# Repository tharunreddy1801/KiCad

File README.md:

# 🛠️ PCB Design Using KiCad

## 📘 Overview

This project demonstrates the complete process of designing a **Printed Circuit Board (PCB)** for a **blinking LED circuit** using a **555 timer IC**. It covers schematic creation, PCB layout, component placement, routing, and final manufacturing file preparation. This guide is ideal for hobbyists and engineers aiming to develop compact and reliable custom PCBs.

---

## 🔍 Project Objective

- Design a PCB to control blinking LEDs using a 555 timer IC  
- Utilize **KiCad**, a free and open-source EDA software  
- Achieve a compact, efficient, and manufacturable PCB design  

---

## ⚙️ System Components

### 📐 Schematic Design
- Complete circuit schematic detailing all component values and connections  
- Ensures correct pin assignments and circuit functionality  

### 🗺️ PCB Layout
- Board outline defined to fit project requirements  
- Components placed for logical routing and ease of manufacturing  
- Focus on:  
  - Signal integrity  
  - Power distribution  
  - Thermal management  

---

## 📸 Design Visualization

---

## ✅ Design Verification

- Design Rule Checks (DRC) performed to identify spacing and connection errors  
- Electrical Rules Checks (ERC) ensure correctness of schematic-to-board mappings  
- Validation to confirm manufacturability and reliability  

---

## 💾 Files Included

- **Schematics:** Detailed circuit diagrams for assembly and troubleshooting  
- **PCB Layout Files:** Component placement and trace routing data  
- **Gerber Files:** Industry-standard output for PCB fabrication  

---

## 🚀 Getting Started

- Open the project files using **KiCad** software suite  
- Follow included documentation for setup and build instructions  
- Review schematic and layout for customization or enhancements  

---

## 👨‍💻 Author

**Yennam Sai Tharun Reddy** ✨

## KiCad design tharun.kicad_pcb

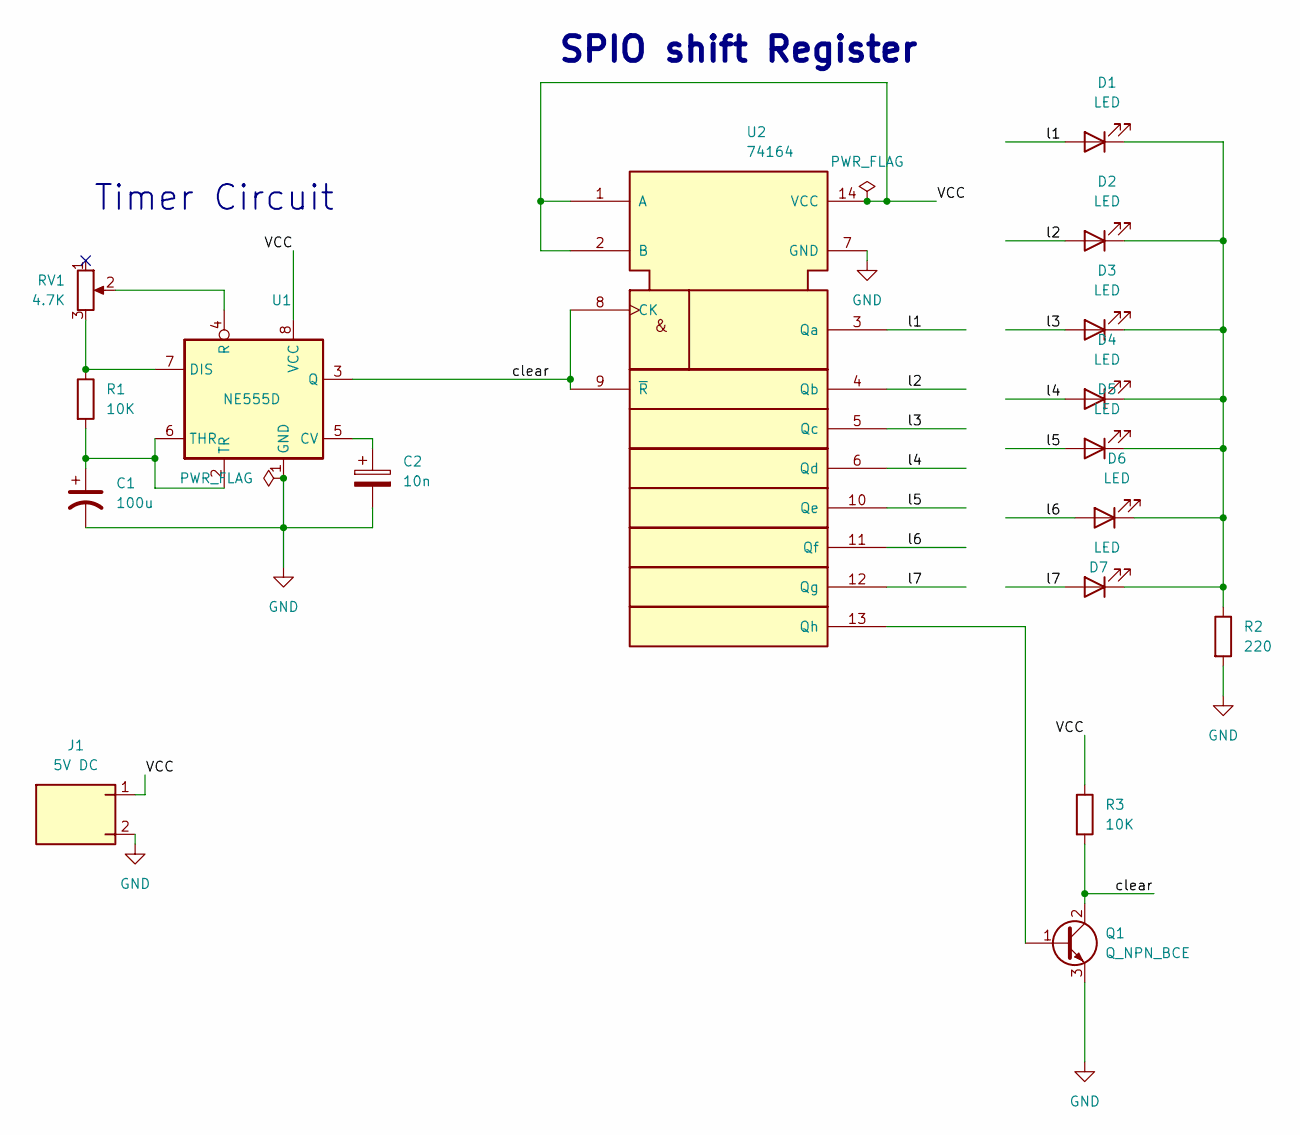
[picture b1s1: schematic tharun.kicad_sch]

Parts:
C1: 100u; C_0201_0603Metric
C2: 10n; C_0201_0603Metric
D1, D2, D3, D4, D5, D6, D7: LED; LED_D3.0mm_Horizontal_O6.35mm_Z10.0mm
J1: 5V DC; BarrelJack_Horizontal
Q1: Q_NPN_BCE; SOT-23-3
R1: 10K; R_0201_0603Metric_Pad0.64x0.40mm_HandSolder
R2: 220; R_0201_0603Metric_Pad0.64x0.40mm_HandSolder
R3: 10K; R_0402_1005Metric
RV1: 4.7K; Potentiometer_ACP_CA14-H5_Horizontal
U1: NE555D; SOIC-8_3.9x4.9mm_P1.27mm
U2: 74164; DIP-14_W7.62mm

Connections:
/VCC: J1.1, R3.1, U1.8 (VCC), U2.1 (A), U2.2 (B), U2.14 (VCC)
/clear: Q1.2 (C), R3.2, U1.3 (Q), U2.8 (CK), U2.9 (~R)
/l1: D1.2 (A), U2.3 (Qa)
/l2: D2.2 (A), U2.4 (Qb)
/l3: D3.2 (A), U2.5 (Qc)
/l4: D4.2 (A), U2.6 (Qd)
/l5: D5.2 (A), U2.10 (Qe)
/l6: D6.2 (A), U2.11 (Qf)
/l7: D7.2 (A), U2.12 (Qg)
GND: C1.2, C2.2, J1.2, Q1.3 (E), R2.2, U1.1 (GND), U2.7 (GND)
unnamed: D1.1 (K), D2.1 (K), D3.1 (K), D4.1 (K), D5.1 (K), D6.1 (K), D7.1 (K), R2.1
unnamed: Q1.1 (B), U2.13 (Qh)
unnamed: C2.1, U1.5 (CV)
unnamed: R1.1, RV1.3, U1.7 (DIS)
unnamed: RV1.2, U1.4 (R)
unnamed: C1.1, R1.2, U1.2 (TR), U1.6 (THR)

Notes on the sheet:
Timer Circuit
SPIO shift Register

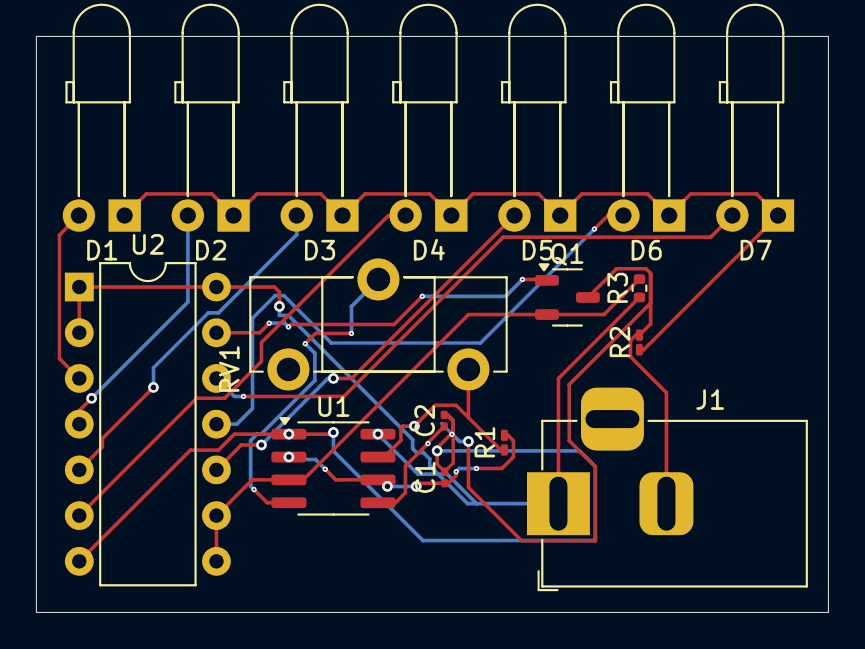
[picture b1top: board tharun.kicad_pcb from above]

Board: 2 copper layers, 44.0 x 32.0 mm, 17 parts (0 on the bottom side), 16 nets.
